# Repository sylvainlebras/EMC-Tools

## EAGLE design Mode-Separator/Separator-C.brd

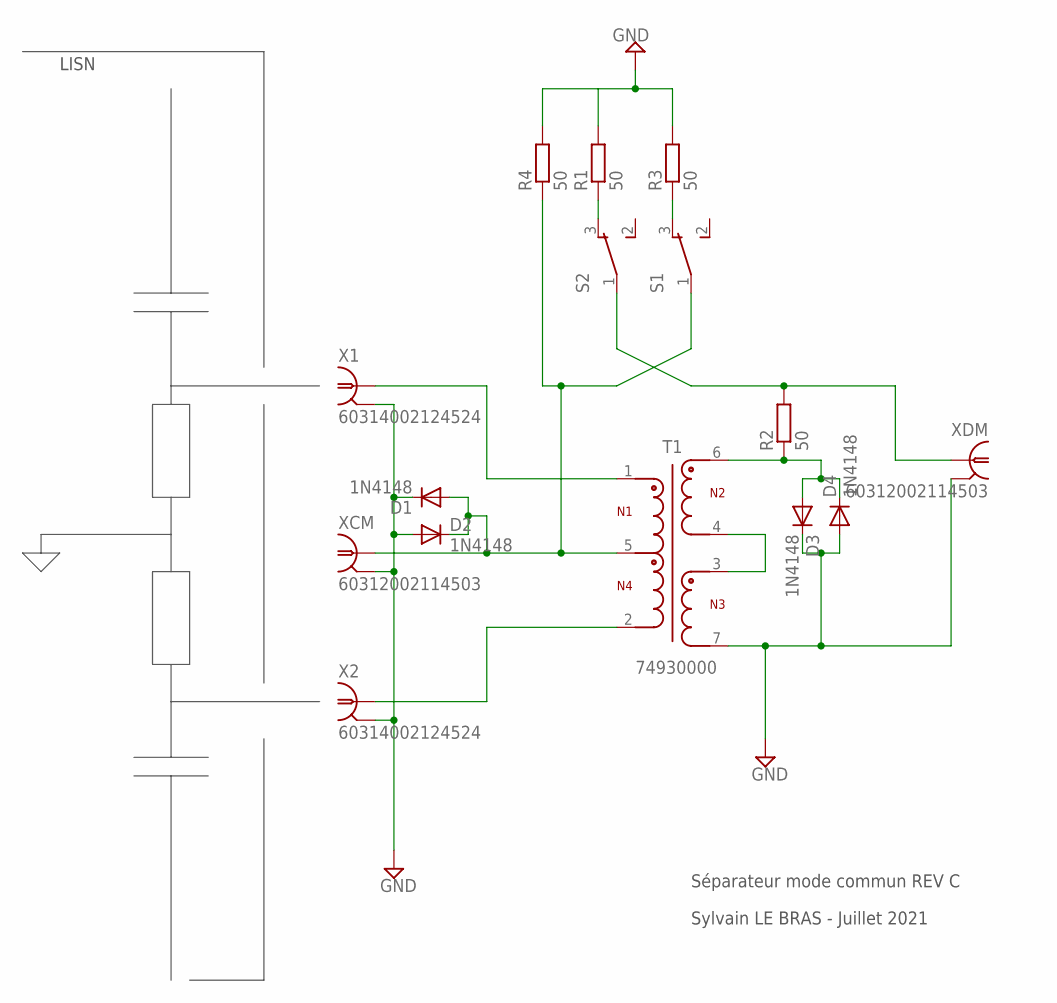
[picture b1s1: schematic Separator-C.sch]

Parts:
D1, D2, D3, D4: 1N4148; SOD123
R1, R2, R3, R4: 50; R0805
S1, S2: 450301014042
T1: 74930000; WE-STST_74930000
X1, X2: 60314002124524; LTI-SASF54GT
XCM: 60312002114503; LTI-SASF54GT
XDM: 60312002114503; LTI-SASF54GT

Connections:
GND: D1.C, D2.A, D3.C, D4.A, R1.2, R3.2, R4.2, T1.7, X1.2 (GND), X1.3 (GND), X1.4 (GND), X1.5 (GND), X2.2 (GND), X2.3 (GND), X2.4 (GND), X2.5 (GND), XCM.2 (GND), XCM.3 (GND), XCM.4 (GND), XCM.5 (GND), XDM.2 (GND), XDM.3 (GND), XDM.4 (GND), XDM.5 (GND)
unnamed: T1.1, X1.1
unnamed: T1.2, X2.1
unnamed: R3.1, S1.3
unnamed: D1.A, D2.C, R4.1, S1.1, T1.5, XCM.1
unnamed: D3.A, D4.C, R2.1, T1.6
unnamed: T1.3, T1.4
unnamed: R1.1, S2.3
unnamed: R2.2, S2.1, XDM.1

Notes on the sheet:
LISN
Séparateur mode commun REV C
Sylvain LE BRAS - Juillet 2021

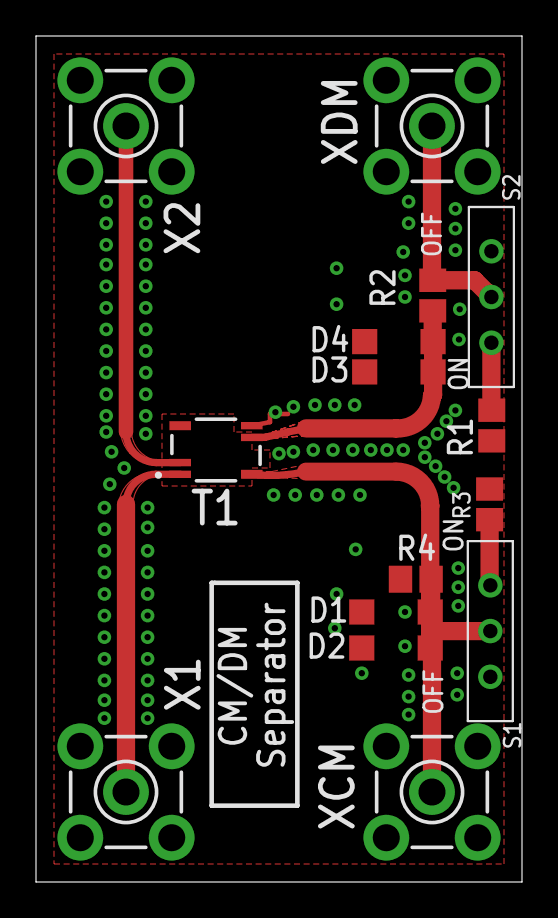
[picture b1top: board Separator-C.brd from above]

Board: 2 copper layers, 27.0 x 47.0 mm, 15 parts (0 on the bottom side), 9 nets.

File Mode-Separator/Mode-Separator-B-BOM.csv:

"Part";"Value";"Device";"Package";"Description";"DATA-RATE";"DATASHEET-URL";"L";"MF";"MOUNT";"MPN";"OC_FARNELL";"OC_NEWARK";"PART-NUMBER";"PORTS";"VT";
"D1";"1N4148";"DIODE-SOD123";"SOD123";"DIODE";"";"";"";"";"";"";"";"";"";"";"";
"D2";"1N4148";"DIODE-SOD123";"SOD123";"DIODE";"";"";"";"";"";"";"";"";"";"";"";
"D3";"1N4148";"DIODE-SOD123";"SOD123";"DIODE";"";"";"";"";"";"";"";"";"";"";"";
"D4";"1N4148";"DIODE-SOD123";"SOD123";"DIODE";"";"";"";"";"";"";"";"";"";"";"";
"R1";"50";"R-EU_R0805";"R0805";"RESISTOR, European symbol";"";"";"";"";"";"";"";"";"";"";"";
"R2";"50";"R-EU_R0805";"R0805";"RESISTOR, European symbol";"";"";"";"";"";"";"";"";"";"";"";
"R3";"50";"R-EU_R0805";"R0805";"RESISTOR, European symbol";"";"";"";"";"";"";"";"";"";"";"";
"R4";"50";"R-EU_R0805";"R0805";"RESISTOR, European symbol";"";"";"";"";"";"";"";"";"";"";"";
"S1";"";"450301014042";"450301014042";"10x2.5 mm THT WS-SLTV";"";"";"";"";"";"";"";"";"";"";"";
"S2";"";"450301014042";"450301014042";"10x2.5 mm THT WS-SLTV";"";"";"";"";"";"";"";"";"";"";"";
"T1";"74930000";"WE-STST_4532_74930000";"WE-STST_74930000";"WE-STST Super Tiny Signal Transformer";"10/100/1000 Base-T, 10/100 Base-T1";"https://katalog.we-online.com/pbs/datasheet/74930000.pdf";"350uH";"";"SMT";"";"";"";" 74930000 ";"1:1";"1500  V (RMS) ";
"X1";"60314002124524";"LTI-SASF54GT";"LTI-SASF54GT";"SMA vertical PCB thrue hole jack";"";"";"";"";"";"";"unknown";"unknown";"";"";"";
"X2";"60314002124524";"LTI-SASF54GT";"LTI-SASF54GT";"SMA vertical PCB thrue hole jack";"";"";"";"";"";"";"unknown";"unknown";"";"";"";
"XCM";"60312002114503";"LTI-SASF54GT";"LTI-SASF54GT";"SMA vertical PCB thrue hole jack";"";"";"";"";"";"";"unknown";"unknown";"";"";"";
"XDM";"60312002114503";"LTI-SASF54GT";"LTI-SASF54GT";"SMA vertical PCB thrue hole jack";"";"";"";"";"";"";"unknown";"unknown";"";"";"";

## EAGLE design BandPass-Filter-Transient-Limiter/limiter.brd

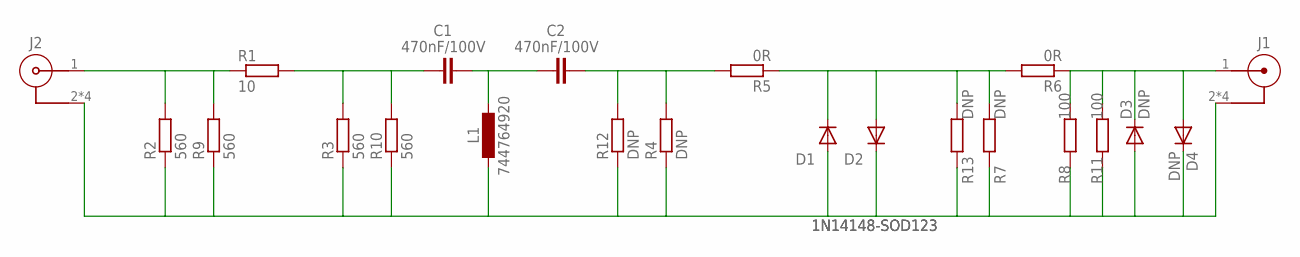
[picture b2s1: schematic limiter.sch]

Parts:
C1, C2: 470nF/100V; C0805K
D1, D2: 1N14148-SOD123; SOD123
D3, D4: DNP; SOD123
J1: 60314202124525
J2: 60312202114509
L1: 744764920; L3225M
R1: 10; R0805
R2, R3, R9, R10: 560; R0805
R4, R7, R12, R13: DNP; R0805
R5, R6: 0R; R0805
R8, R11: 100; R0805

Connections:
GND: D1.A, D2.C, D3.A, D4.C, J1.2, J1.3 (2), J1.4 (2), J1.5 (2), J2.2, J2.3 (2), J2.4 (2), J2.5 (2), L1.2, R2.1, R3.1, R4.1, R7.2, R8.2, R9.1, R10.1, R11.2, R12.1, R13.2
unnamed: J2.1, R1.1, R2.2, R9.2
unnamed: C1.1, R1.2, R3.2, R10.2
unnamed: C1.2, C2.1, L1.1
unnamed: C2.2, R4.2, R5.2, R12.2
unnamed: D1.C, D2.A, R5.1, R6.2, R7.1, R13.1
unnamed: D3.C, D4.A, J1.1, R6.1, R8.1, R11.1

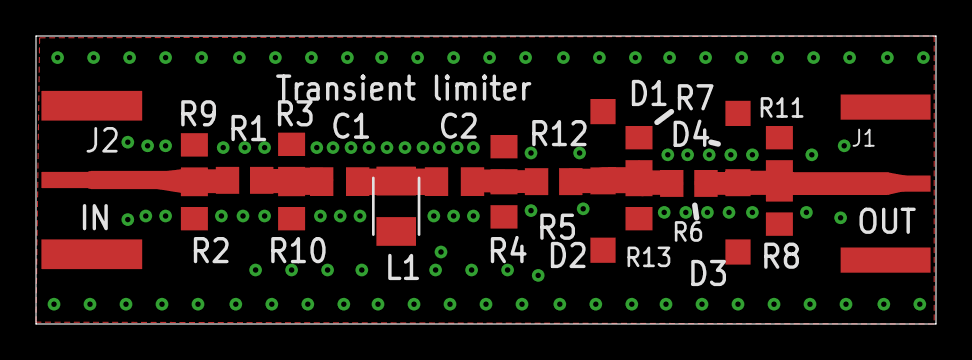
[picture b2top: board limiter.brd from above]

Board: 2 copper layers, 50.0 x 16.0 mm, 22 parts (0 on the bottom side), 7 nets.

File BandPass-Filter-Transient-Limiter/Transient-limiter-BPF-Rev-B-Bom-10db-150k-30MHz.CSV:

"Part";"Value";"Device";"Package";"Description";"DATASHEET-URL";"GENDER";"INTERFACE";"MOUNT";"ORIENTATION-TYPE";"PART-NUMBER";"Z";
"C1";"470nF/100V";"C-EUC0805K";"C0805K";"CAPACITOR, European symbol";"";"";"";"";"";"";"";
"C2";"470nF/100V";"C-EUC0805K";"C0805K";"CAPACITOR, European symbol";"";"";"";"";"";"";"";
"D1";"1N14148-SOD123";"DIODE-SOD123";"SOD123";"DIODE";"";"";"";"";"";"";"";
"D2";"1N14148-SOD123";"DIODE-SOD123";"SOD123";"DIODE";"";"";"";"";"";"";"";
"D3";"DNP";"DIODE-SOD123";"SOD123";"DIODE";"";"";"";"";"";"";"";
"D4";"DNP";"DIODE-SOD123";"SOD123";"DIODE";"";"";"";"";"";"";"";
"J1";"";"60314202124525";"60314202124525";"WR-SMA PCB End Launch Plug Round Post 1.6 mm";"https://katalog.we-online.com/em/datasheet/60314202124525.pdf";"Plug";"MIL-STD-348";"End Launch";"Straight";"60314202124525";"50Ohm";
"J2";"";"60312202114509";"60312202114509";"WR-SMA PCB End Launch Jack Round Post 1.6 mm";"https://katalog.we-online.com/em/datasheet/60312202114509.pdf";"Jack";"MIL-STD-348";"End Launch";"Straight";"60312202114509";"50Ohm";
"L1";"744764920";"L-EUL3225M";"L3225M";"INDUCTOR, European symbol";"";"";"";"";"";"";"";
"R1";"10";"R-EU_R0805";"R0805";"RESISTOR, European symbol";"";"";"";"";"";"";"";
"R2";"560";"R-EU_R0805";"R0805";"RESISTOR, European symbol";"";"";"";"";"";"";"";
"R3";"560";"R-EU_R0805";"R0805";"RESISTOR, European symbol";"";"";"";"";"";"";"";
"R4";"DNP";"R-EU_R0805";"R0805";"RESISTOR, European symbol";"";"";"";"";"";"";"";
"R5";"0R";"R-EU_R0805";"R0805";"RESISTOR, European symbol";"";"";"";"";"";"";"";
"R6";"0R";"R-EU_R0805";"R0805";"RESISTOR, European symbol";"";"";"";"";"";"";"";
"R7";"DNP";"R-EU_R0805";"R0805";"RESISTOR, European symbol";"";"";"";"";"";"";"";
"R8";"100";"R-EU_R0805";"R0805";"RESISTOR, European symbol";"";"";"";"";"";"";"";
"R9";"560";"R-EU_R0805";"R0805";"RESISTOR, European symbol";"";"";"";"";"";"";"";
"R10";"560";"R-EU_R0805";"R0805";"RESISTOR, European symbol";"";"";"";"";"";"";"";
"R11";"100";"R-EU_R0805";"R0805";"RESISTOR, European symbol";"";"";"";"";"";"";"";
"R12";"DNP";"R-EU_R0805";"R0805";"RESISTOR, European symbol";"";"";"";"";"";"";"";
"R13";"DNP";"R-EU_R0805";"R0805";"RESISTOR, European symbol";"";"";"";"";"";"";"";

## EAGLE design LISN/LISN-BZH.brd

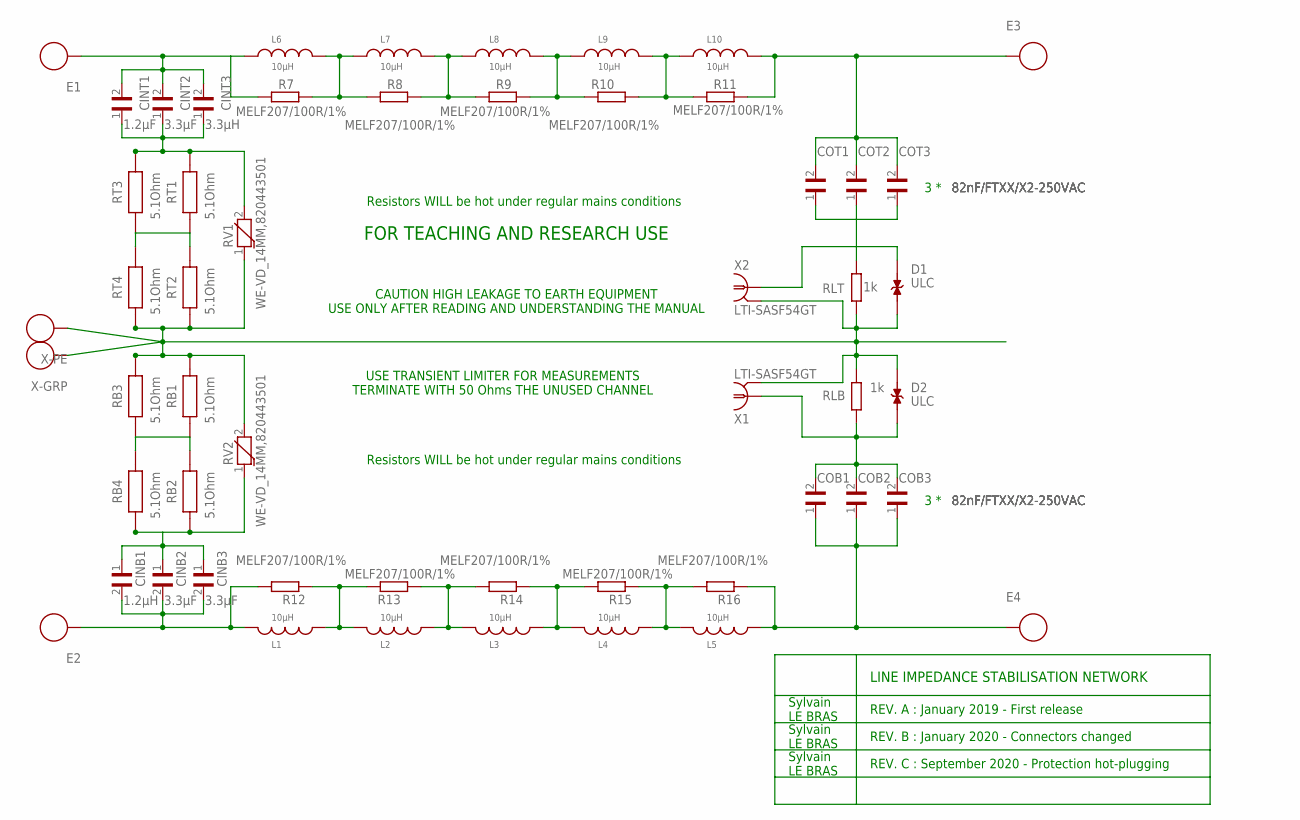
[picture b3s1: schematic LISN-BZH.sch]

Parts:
CINB1: 1.2µH; WCAP-FTXX_27.5X31X29X15.5
CINB2, CINB3: 3.3µF; WCAP-FTXX_27.5X31X29X15.5
CINT1: 1.2µF; WCAP-FTXX_27.5X31X29X15.5
CINT2: 3.3µF; WCAP-FTXX_27.5X31X29X15.5
CINT3: 3.3µH; WCAP-FTXX_27.5X31X29X15.5
COB1, COB2, COB3: 82nF/FTXX/X2-250VAC; WCAP-FTXX_10X13X13X7
COT1, COT2, COT3: 82nF/FTXX/X2-250VAC; WCAP-FTXX_10X13X13X7
D1, D2: ULC; WE-VE_ULC_0603
E1, E2, E3, E4: WP-PLUG_7464000; PLUG
L1, L2, L3, L4, L5, L6, L7, L8, L9, L10: 10µH; WE-HCC_1210
R7, R8, R9, R10, R11, R12, R13, R14, R15, R16: MELF207/100R/1%; MINI_MELF-0207R
RB1, RB2, RB3, RB4: 5.1Ohm; WRIS-KWKB_1225
RLB: 1k; M0805
RLT: 1k; M0805
RT1, RT2, RT3, RT4: 5.1Ohm; WRIS-KWKB_1225
RV1, RV2: WE-VD_14MM,820443501; WE-VD_14MM-0.9
X1, X2: LTI-SASF54GT
X-GRP: WP-THRSH_74651175(R); THRXU_1.85_4PINS_7X7
X-PE: WP-THRSH_74651175(R); THRXU_1.85_4PINS_7X7

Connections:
GND: D1.2, D2.2, RB1.2, RB3.2, RLB.1, RLT.1, RT2.1, RT4.1, RV1.1, RV2.2, X1.2 (GND), X1.3 (GND), X1.4 (GND), X1.5 (GND), X2.2 (GND), X2.3 (GND), X2.4 (GND), X2.5 (GND), X-GRP.1, X-GRP.2, X-GRP.3, X-GRP.4, X-PE.1, X-PE.2, X-PE.3, X-PE.4
GND1: CINB1.1, CINB2.1, CINB3.1, RB2.1, RB4.1, RV2.1
unnamed: CINT1.1, CINT2.1, CINT3.1, RT1.2, RT3.2, RV1.2
unnamed: L9.2, L10.1, R10.1, R11.2
unnamed: L4.2, L5.1, R15.1, R16.2
unnamed: L3.2, L4.1, R14.1, R15.2
unnamed: L2.2, L3.1, R13.1, R14.2
unnamed: L1.2, L2.1, R12.1, R13.2
unnamed: COB1.1, COB2.1, COB3.1, E4.1, E4.2, E4.3, E4.4, E4.5, E4.6, E4.7, E4.8, E4.9, E4.10, E4.11, E4.12, L5.2, R16.1
unnamed: CINB1.2, CINB2.2, CINB3.2, E2.1, E2.2, E2.3, E2.4, E2.5, E2.6, E2.7, E2.8, E2.9, E2.10, E2.11, E2.12, L1.1, R12.2
unnamed: L8.2, L9.1, R9.1, R10.2
unnamed: COB1.2, COB2.2, COB3.2, D2.1, RLB.2, X1.1
unnamed: L7.2, L8.1, R8.1, R9.2
unnamed: L6.2, L7.1, R7.1, R8.2
unnamed: COT1.2, COT2.2, COT3.2, E3.1, E3.2, E3.3, E3.4, E3.5, E3.6, E3.7, E3.8, E3.9, E3.10, E3.11, E3.12, L10.2, R11.1
unnamed: CINT1.2, CINT2.2, CINT3.2, E1.1, E1.2, E1.3, E1.4, E1.5, E1.6, E1.7, E1.8, E1.9, E1.10, E1.11, E1.12, L6.1, R7.2
unnamed: COT1.1, COT2.1, COT3.1, D1.1, RLT.2, X2.1
unnamed: RT1.1, RT2.2, RT3.1, RT4.2
unnamed: RB1.1, RB2.2, RB3.1, RB4.2

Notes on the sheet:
FOR TEACHING AND RESEARCH USE
CAUTION HIGH LEAKAGE TO EARTH EQUIPMENT USE ONLY AFTER READING AND UNDERSTANDING THE MANUAL
Resistors WILL be hot under regular mains conditions
LINE IMPEDANCE STABILISATION NETWORK
REV. A : January 2019 - First release
Sylvain LE BRAS
USE TRANSIENT LIMITER FOR MEASUREMENTS TERMINATE WITH 50 Ohms THE UNUSED CHANNEL
3 *
REV. B : January 2020 - Connectors changed
REV. C : September 2020 - Protection hot-plugging

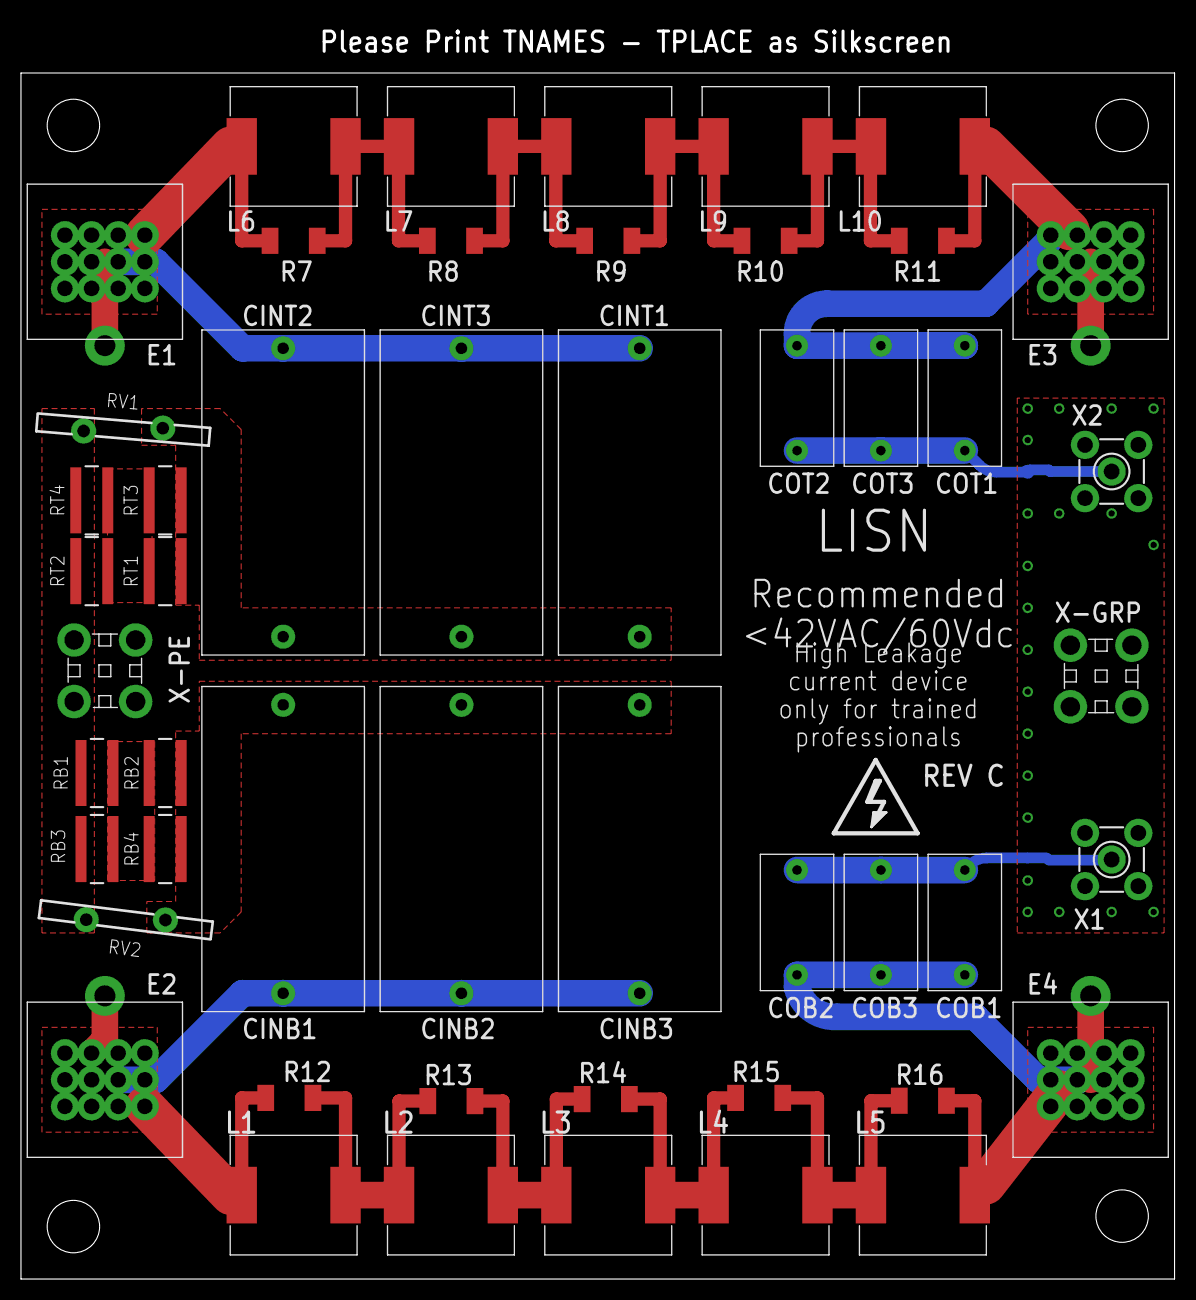
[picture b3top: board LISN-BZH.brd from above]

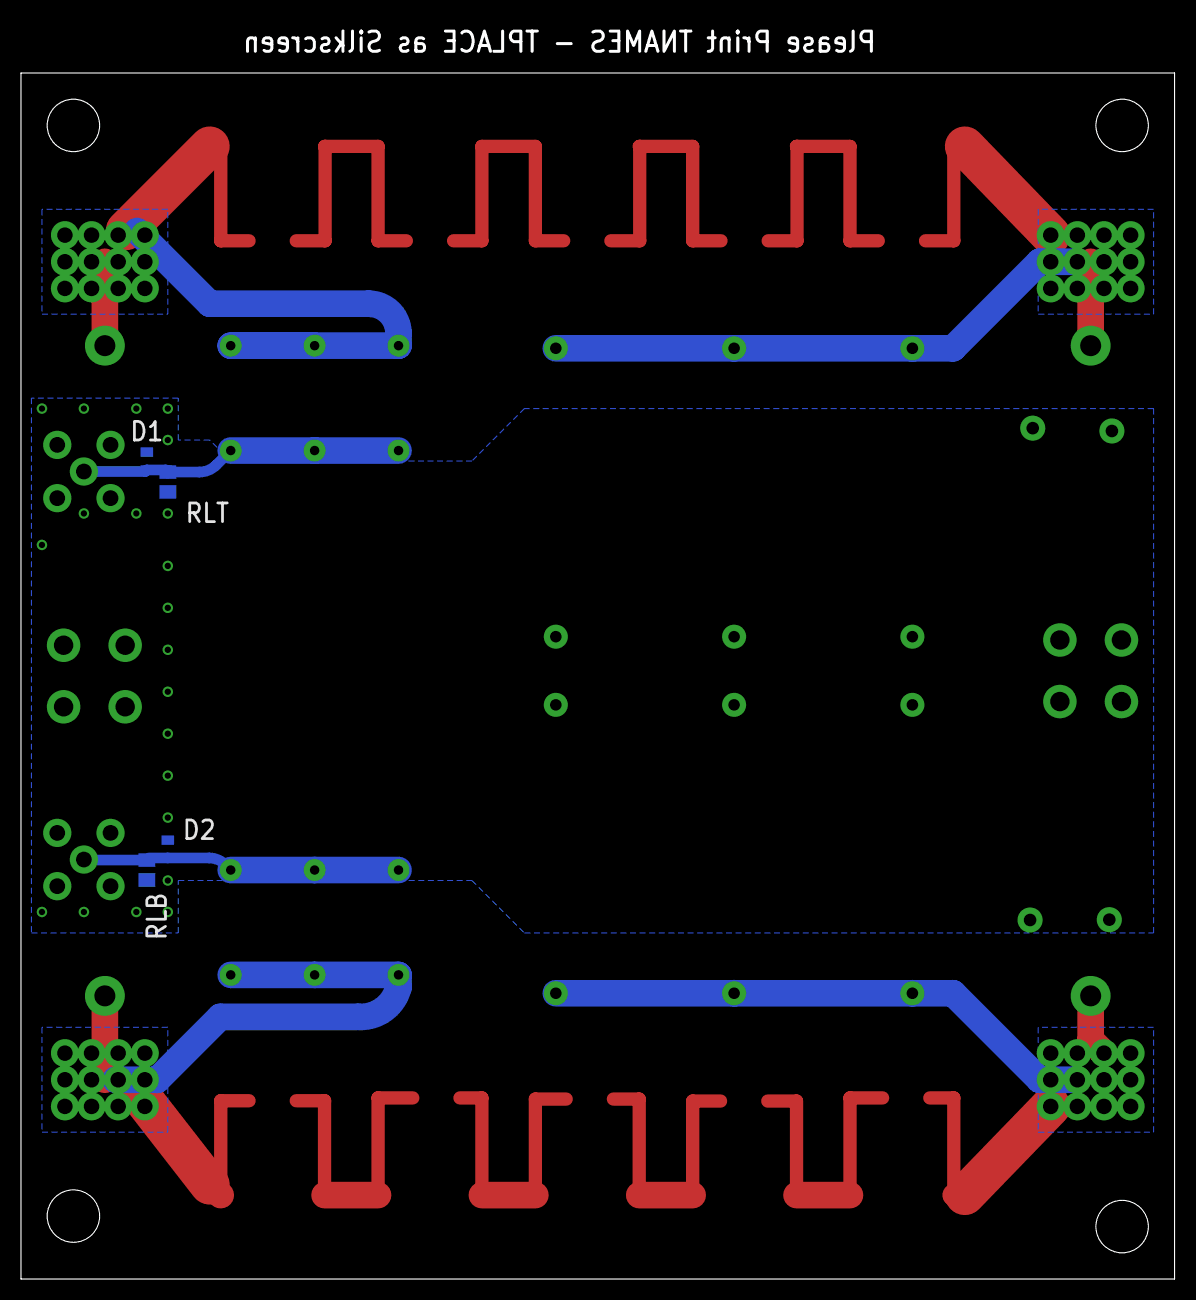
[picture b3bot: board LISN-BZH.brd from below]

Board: 2 copper layers, 110.0 x 120.0 mm, 54 parts (4 on the bottom side), 19 nets.

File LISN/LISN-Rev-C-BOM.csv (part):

"Part";"Value";"Device";"Package";"Description";"COMPANY-URL";"CREATED-BY";"CREATED-DATE";"DATASHEET-URL";"IR";"MANUFACTURER";"MF";"MOUNT";"MPN";"OC_FARNELL";"OC_NEWARK";"PART-NUMBER";"PRATED";"TCR";"TECHNICAL-REFERENCE";"VALUE";"WE-NUMBER";
"CINB1";"1.2µH";"WCAP-FTXX_890334027025";"WCAP-FTXX_27.5X31X29X15.5";"WCAP-FTXX Film Capacitors";"";"";"";"";"";"";"";"";"";"";"";"";"";"";"";"";"";
"CINB2";"3.3µF";"WCAP-FTXX_890334027025";"WCAP-FTXX_27.5X31X29X15.5";"WCAP-FTXX Film Capacitors";"";"";"";"";"";"";"";"";"";"";"";"";"";"";"";"";"";
"CINB3";"3.3µF";"WCAP-FTXX_890334027025";"WCAP-FTXX_27.5X31X29X15.5";"WCAP-FTXX Film Capacitors";"";"";"";"";"";"";"";"";"";"";"";"";"";"";"";"";"";
"CINT1";"1.2µF";"WCAP-FTXX_890334027025";"WCAP-FTXX_27.5X31X29X15.5";"WCAP-FTXX Film Capacitors";"";"";"";"";"";"";"";"";"";"";"";"";"";"";"";"";"";
"CINT2";"3.3µF";"WCAP-FTXX_890334027025";"WCAP-FTXX_27.5X31X29X15.5";"WCAP-FTXX Film Capacitors";"";"";"";"";"";"";"";"";"";"";"";"";"";"";"";"";"";
"CINT3";"3.3µH";"WCAP-FTXX_890334027025";"WCAP-FTXX_27.5X31X29X15.5";"WCAP-FTXX Film Capacitors";"";"";"";"";"";"";"";"";"";"";"";"";"";"";"";"";"";
"COB1";"82nF/FTXX/X2-250VAC";"WCAP-FTXX_890334023019";"WCAP-FTXX_10X13X13X7";"WCAP-FTXX Film Capacitors";"";"";"";"";"";"";"";"";"";"";"";"";"";"";"";"";"";
"COB2";"82nF/FTXX/X2-250VAC";"WCAP-FTXX_890334023019";"WCAP-FTXX_10X13X13X7";"WCAP-FTXX Film Capacitors";"";"";"";"";"";"";"";"";"";"";"";"";"";"";"";"";"";
"COB3";"82nF/FTXX/X2-250VAC";"WCAP-FTXX_890334023019";"WCAP-FTXX_10X13X13X7";"WCAP-FTXX Film Capacitors";"";"";"";"";"";"";"";"";"";"";"";"";"";"";"";"";"";
"COT1";"82nF/FTXX/X2-250VAC";"WCAP-FTXX_890334023019";"WCAP-FTXX_10X13X13X7";"WCAP-FTXX Film Capacitors";"";"";"";"";"";"";"";"";"";"";"";"";"";"";"";"";"";
"COT2";"82nF/FTXX/X2-250VAC";"WCAP-FTXX_890334023019";"WCAP-FTXX_10X13X13X7";"WCAP-FTXX Film Capacitors";"";"";"";"";"";"";"";"";"";"";"";"";"";"";"";"";"";
"COT3";"82nF/FTXX/X2-250VAC";"WCAP-FTXX_890334023019";"WCAP-FTXX_10X13X13X7";"WCAP-FTXX Film Capacitors";"";"";"";"";"";"";"";"";"";"";"";"";"";"";"";"";"";
"D1";"ULC";"WE-VE_ULC_0603_82306050029";"WE-VE_ULC_0603";"WE-VE ULC ESD Suppressor";"";"";"";"";"";"";"";"";"";"";"";"";"";"";"";"";"";
"D2";"ULC";"WE-VE_ULC_0603_82306050029";"WE-VE_ULC_0603";"WE-VE ULC ESD Suppressor";"";"";"";"";"";"";"";"";"";"";"";"";"";"";"";"";"";
"E1";"";"WP-PLUG_7464000";"PLUG";"REDCUBE Plug Terminal WP-PLUG";"";"";"";"";"";"";"";"";"";"";"";"";"";"";"";"";"";
"E2";"";"WP-PLUG_7464000";"PLUG";"REDCUBE Plug Terminal WP-PLUG";"";"";"";"";"";"";"";"";"";"";"";"";"";"";"";"";"";
"E3";"";"WP-PLUG_7464000";"PLUG";"REDCUBE Plug Terminal WP-PLUG";"";"";"";"";"";"";"";"";"";"";"";"";"";"";"";"";"";
"E4";"";"WP-PLUG_7464000";"PLUG";"REDCUBE Plug Terminal WP-PLUG";"";"";"";"";"";"";"";"";"";"";"";"";"";"";"";"";"";
"L1";"10µH";"WE-HCC_1210_7443321000";"WE-HCC_1210";"SMD High Current Cube Inductor";"";"";"";"";"";"";"";"";"";"";"";"";"";"";"";"";"7443321000/10uH";
"L2";"10µH";"WE-HCC_1210_7443321000";"WE-HCC_1210";"SMD High Current Cube Inductor";"";"";"";"";"";"";"";"";"";"";"";"";"";"";"";"";"7443321000/10uH";
"L3";"10µH";"WE-HCC_1210_7443321000";"WE-HCC_1210";"SMD High Current Cube Inductor";"";"";"";"";"";"";"";"";"";"";"";"";"";"";"";"";"7443321000/10uH";
"L4";"10µH";"WE-HCC_1210_7443321000";"WE-HCC_1210";"SMD High Current Cube Inductor";"";"";"";"";"";"";"";"";"";"";"";"";"";"";"";"";"7443321000/10uH";
"L5";"10µH";"WE-HCC_1210_7443321000";"WE-HCC_1210";"SMD High Current Cube Inductor";"";"";"";"";"";"";"";"";"";"";"";"";"";"";"";"";"7443321000/10uH";
"L6";"10µH";"WE-HCC_1210_7443321000";"WE-HCC_1210";"SMD High Current Cube Inductor";"";"";"";"";"";"";"";"";"";"";"";"";"";"";"";"";"7443321000/10uH";
"L7";"10µH";"WE-HCC_1210_7443321000";"WE-HCC_1210";"SMD High Current Cube Inductor";"";"";"";"";"";"";"";"";"";"";"";"";"";"";"";"";"7443321000/10uH";
"L8";"10µH";"WE-HCC_1210_7443321000";"WE-HCC_1210";"SMD High Current Cube Inductor";"";"";"";"";"";"";"";"";"";"";"";"";"";"";"";"";"7443321000/10uH";
"L9";"10µH";"WE-HCC_1210_7443321000";"WE-HCC_1210";"SMD High Current Cube Inductor";"";"";"";"";"";"";"";"";"";"";"";"";"";"";"";"";"7443321000/10uH";
"L10";"10µH";"WE-HCC_1210_7443321000";"WE-HCC_1210";"SMD High Current Cube Inductor";"";"";"";"";"";"";"";"";"";"";"";"";"";"";"";"";"7443321000/10uH";
"R7";"MELF207/100R/1%";"R-EU_MELF0207R";"MINI_MELF-0207R";"RESISTOR, European symbol";"";"";"";"";"";"";"";"";"";"";"";"";"";"";"";"";"";
"R8";"MELF207/100R/1%";"R-EU_MELF0207R";"MINI_MELF-0207R";"RESISTOR, European symbol";"";"";"";"";"";"";"";"";"";"";"";"";"";"";"";"";"";
"R9";"MELF207/100R/1%";"R-EU_MELF0207R";"MINI_MELF-0207R";"RESISTOR, European symbol";"";"";"";"";"";"";"";"";"";"";"";"";"";"";"";"";"";
"R10";"MELF207/100R/1%";"R-EU_MELF0207R";"MINI_MELF-0207R";"RESISTOR, European symbol";"";"";"";"";"";"";"";"";"";"";"";"";"";"";"";"";"";
"R11";"MELF207/100R/1%";"R-EU_MELF0207R";"MINI_MELF-0207R";"RESISTOR, European symbol";"";"";"";"";"";"";"";"";"";"";"";"";"";"";"";"";"";
"R12";"MELF207/100R/1%";"R-EU_MELF0207R";"MINI_MELF-0207R";"RESISTOR, European symbol";"";"";"";"";"";"";"";"";"";"";"";"";"";"";"";"";"";
"R13";"MELF207/100R/1%";"R-EU_MELF0207R";"MINI_MELF-0207R";"RESISTOR, European symbol";"";"";"";"";"";"";"";"";"";"";"";"";"";"";"";"";"";
"R14";"MELF207/100R/1%";"R-EU_MELF0207R";"MINI_MELF-0207R";"RESISTOR, European symbol";"";"";"";"";"";"";"";"";"";"";"";"";"";"";"";"";"";
"R15";"MELF207/100R/1%";"R-EU_MELF0207R";"MINI_MELF-0207R";"RESISTOR, European symbol";"";"";"";"";"";"";"";"";"";"";"";"";"";"";"";"";"";
"R16";"MELF207/100R/1%";"R-EU_MELF0207R";"MINI_MELF-0207R";"RESISTOR, European symbol";"";"";"";"";"";"";"";"";"";"";"";"";"";"";"";"";"";
"RB1";"5.1Ohm";"WRIS-KWKB_1225_561020163017";"WRIS-KWKB_1225";"WRIS-KWKB Thick Film Resistors";"";"";"";"https://katalog.we-online.de/pbs/datasheet/561020163017.pdf";"626.2mA";"";"";"SMT";"";"";"";" 561020163017 ";"2W";"±200ppm/ °C";"KB12255R10F201DAATE0000";"5.1Ohm";"";
"RB2";"5.1Ohm";"WRIS-KWKB_1225_561020163017";"WRIS-KWKB_1225";"WRIS-KWKB Thick Film Resistors";"";"";"";"https://katalog.we-online.de/pbs/datasheet/561020163017.pdf";"626.2mA";"";"";"SMT";"";"";"";" 561020163017 ";"2W";"±200ppm/ °C";"KB12255R10F201DAATE0000";"5.1Ohm";"";
"RB3";"5.1Ohm";"WRIS-KWKB_1225_561020163017";"WRIS-KWKB_1225";"WRIS-KWKB Thick Film Resistors";"";"";"";"https://katalog.we-online.de/pbs/datasheet/561020163017.pdf";"626.2mA";"";"";"SMT";"";"";"";" 561020163017 ";"2W";"±200ppm/ °C";"KB12255R10F201DAATE0000";"5.1Ohm";"";
"RB4";"5.1Ohm";"WRIS-KWKB_1225_561020163017";"WRIS-KWKB_1225";"WRIS-KWKB Thick Film Resistors";"";"";"";"https://katalog.we-online.de/pbs/datasheet/561020163017.pdf";"626.2mA";"";"";"SMT";"";"";"";" 561020163017 ";"2W";"±200ppm/ °C";"KB12255R10F201DAATE0000";"5.1Ohm";"";
"RLB";"1k";"R-EU_M0805";"M0805";"RESISTOR, European symbol";"";"";"";"";"";"";"";"";"";"";"";"";"";"";"";"";"";
"RLT";"1k";"R-EU_M0805";"M0805";"RESISTOR, European symbol";"";"";"";"";"";"";"";"";"";"";"";"";"";"";"";"";"";
"RT1";"5.1Ohm";"WRIS-KWKB_1225_561020163017";"WRIS-KWKB_1225";"WRIS-KWKB Thick Film Resistors";"";"";"";"https://katalog.we-online.de/pbs/datasheet/561020163017.pdf";"626.2mA";"";"";"SMT";"";"";"";" 561020163017 ";"2W";"±200ppm/ °C";"KB12255R10F201DAATE0000";"5.1Ohm";"";
"RT2";"5.1Ohm";"WRIS-KWKB_1225_561020163017";"WRIS-KWKB_1225";"WRIS-KWKB Thick Film Resistors";"";"";"";"https://katalog.we-online.de/pbs/datasheet/561020163017.pdf";"626.2mA";"";"";"SMT";"";"";"";" 561020163017 ";"2W";"±200ppm/ °C";"KB12255R10F201DAATE0000";"5.1Ohm";"";
"RT3";"5.1Ohm";"WRIS-KWKB_1225_561020163017";"WRIS-KWKB_1225";"WRIS-KWKB Thick Film Resistors";"";"";"";"https://katalog.we-online.de/pbs/datasheet/561020163017.pdf";"626.2mA";"";"";"SMT";"";"";"";" 561020163017 ";"2W";"±200ppm/ °C";"KB12255R10F201DAATE0000";"5.1Ohm";"";
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
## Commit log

2020-11-03 Initial Commit
    All the tools for training, investigation and teaching of EMC. Feel free to ask questions, manual will follow
2021-07-11 Rev C, correction of short circuit in rev B
    There was two vias shorting a track on version B (between S2 and R2). Version C has been corrected.
2021-07-11 There Was an error in Gerber
2021-07-11 There Was an error in RevB
2021-07-11 Rename Mode-Separator-B-BOM.csv to Mode-Separator-C-BOM.csv
    There Was an error in RevB, no change on BOM but renamed for consistency
2023-06-14 Limit lines and SVG visulisation
    Getting ready for article 2 and update of article 1
2023-10-23 Initial commit
    Released old design used for teaching
    Updated connector
2023-10-23 Gerber Export

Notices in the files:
parts and their libraries:
60312202111527_Eagle_WR-SMA_rev19a: Copyright: Würth Elektronik
